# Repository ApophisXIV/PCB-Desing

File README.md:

# PCB-Desing
In this repo you'll find some PCBs I have designed across several years for differents projects

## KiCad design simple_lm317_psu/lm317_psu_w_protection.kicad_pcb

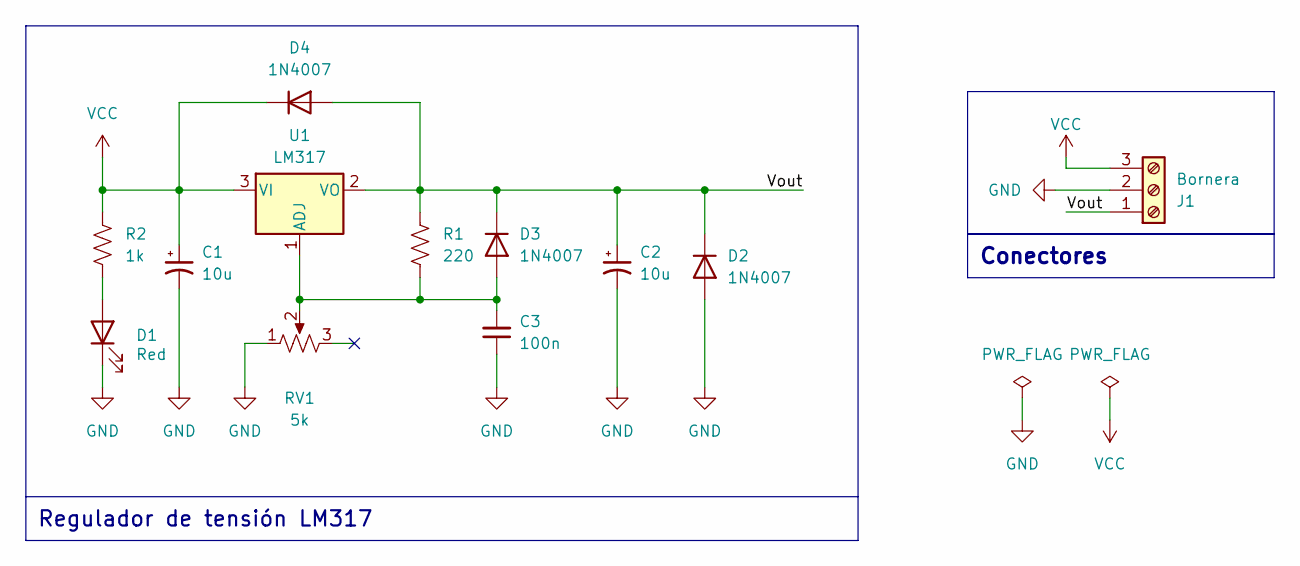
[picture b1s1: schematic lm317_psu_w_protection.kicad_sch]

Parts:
C1, C2: 10u; CP_Radial_D5.0mm_P2.00mm
C3: 100n; C_Disc_D5.0mm_W2.5mm_P2.50mm
D1: Red; LED_D5.0mm
D2, D3, D4: 1N4007; D_DO-41_SOD81_P10.16mm_Horizontal
J1: Bornera; TerminalBlock_bornier-3_P5.08mm
R1: 220; R_Axial_DIN0207_L6.3mm_D2.5mm_P7.62mm_Horizontal
R2: 1k; R_Axial_DIN0207_L6.3mm_D2.5mm_P7.62mm_Horizontal
RV1: 5k; Potentiometer_Alps_RK163_Single_Horizontal
U1: LM317; TO-220-3_Vertical

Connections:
/Vout: C2.1, D2.1 (K), D3.1 (K), D4.2 (A), J1.1, R1.1, U1.2 (VO)
GND: C1.2, C2.2, C3.1, D1.1 (K), D2.2 (A), J1.2, RV1.1
unnamed: D1.2 (A), R2.2
unnamed: C3.2, D3.2 (A), R1.2, RV1.2, U1.1 (ADJ)
VCC: C1.1, D4.1 (K), J1.3, R2.1, U1.3 (VI)

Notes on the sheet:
Conectores
Regulador de tensión LM317

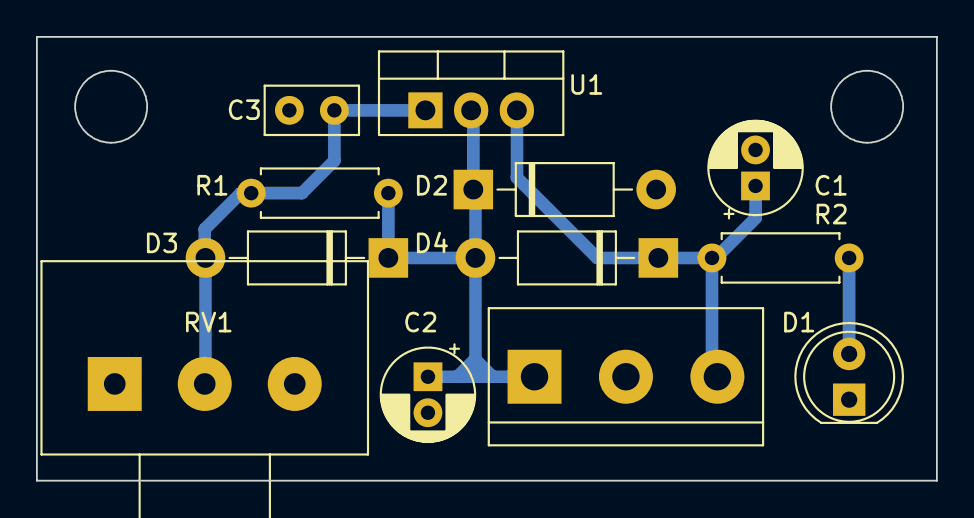
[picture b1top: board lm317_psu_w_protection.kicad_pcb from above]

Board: 2 copper layers, 50.0 x 24.7 mm, 12 parts (0 on the bottom side), 5 nets.

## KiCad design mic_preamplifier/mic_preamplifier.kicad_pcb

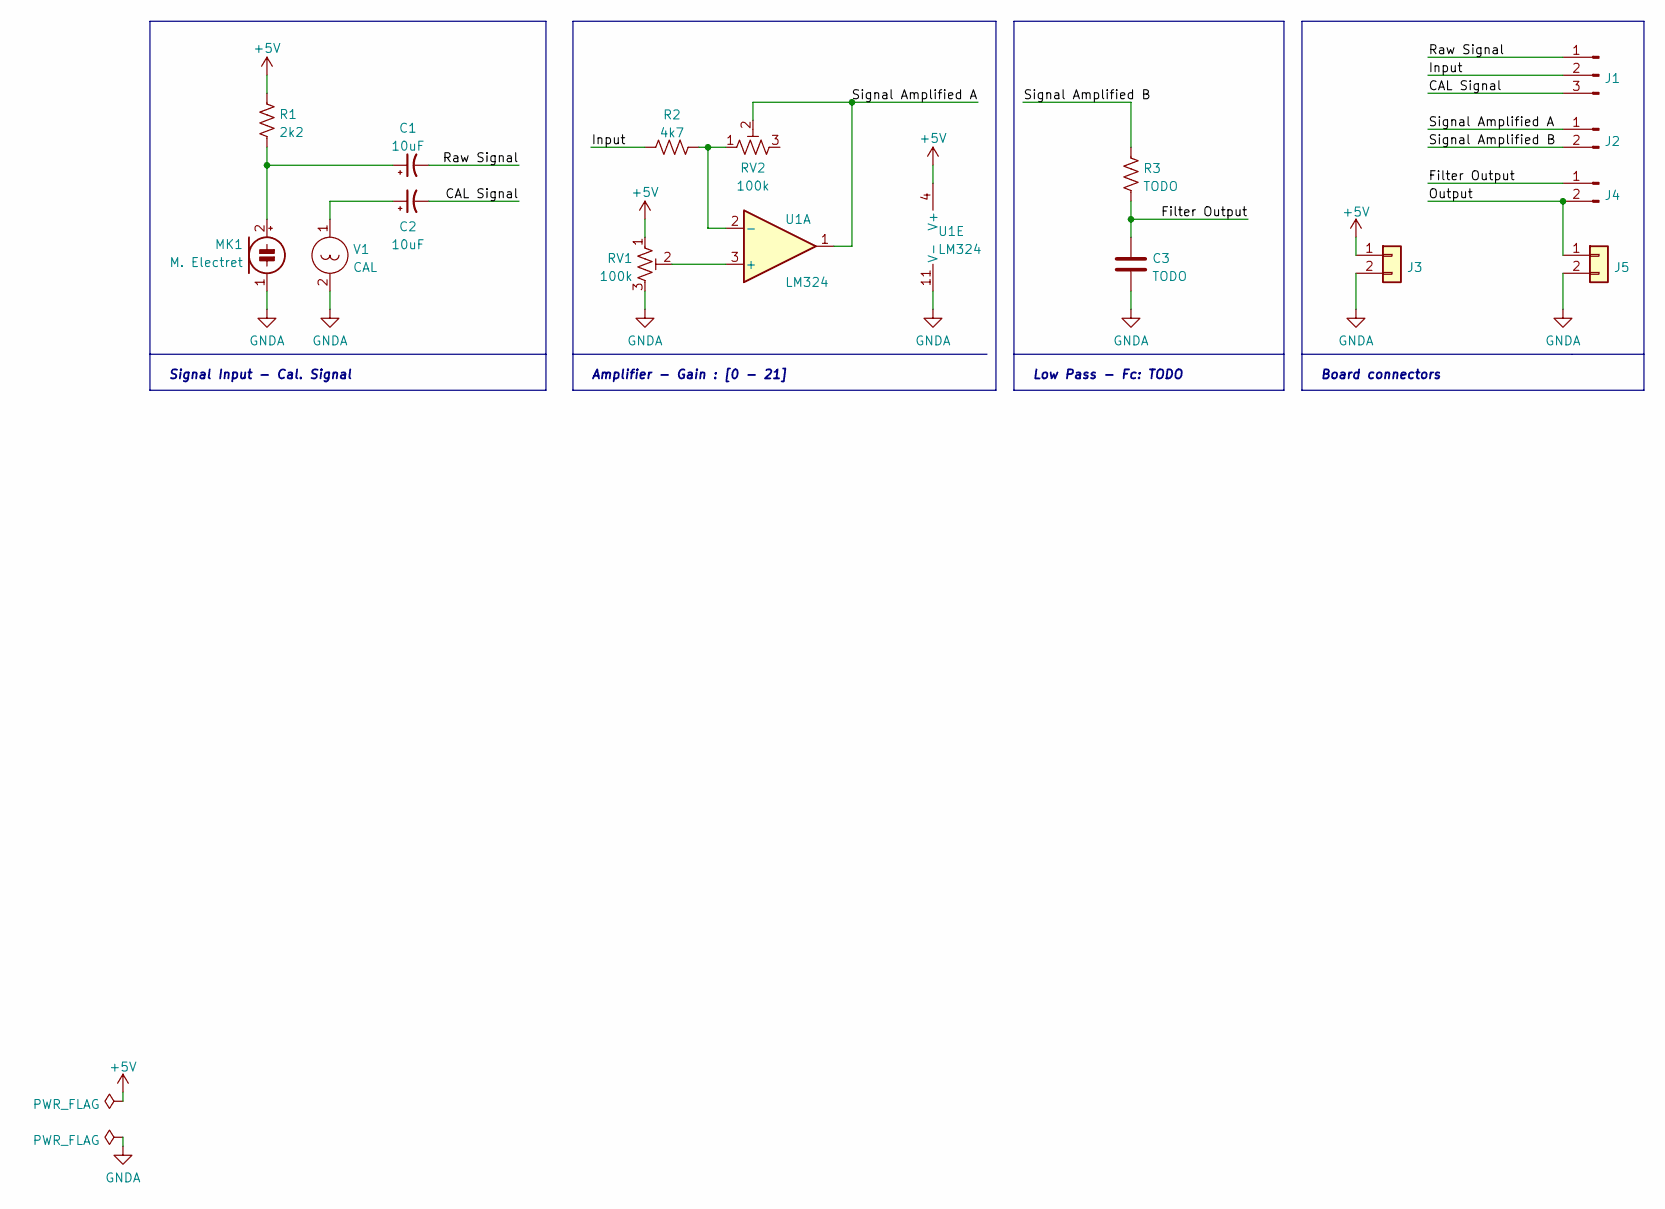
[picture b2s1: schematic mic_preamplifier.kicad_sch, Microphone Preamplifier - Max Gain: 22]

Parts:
C1, C2: 10uF; CP_Radial_D4.0mm_P2.00mm
C3: TODO; C_Disc_D3.8mm_W2.6mm_P2.50mm
J1: Conn_01x03_Male; PinHeader_1x03_P2.54mm_Vertical
J2, J4: Conn_01x02_Male; PinHeader_1x02_P2.54mm_Vertical
J3, J5: Conn_01x02; TerminalBlock_bornier-2_P5.08mm
MK1: M. Electret; PinHeader_1x02_P2.54mm_Vertical
R1: 2k2; R_Axial_DIN0207_L6.3mm_D2.5mm_P10.16mm_Horizontal
R2: 4k7; R_Axial_DIN0207_L6.3mm_D2.5mm_P10.16mm_Horizontal
R3: TODO; R_Axial_DIN0207_L6.3mm_D2.5mm_P10.16mm_Horizontal
RV1, RV2: 100k; Potentiometer_Bourns_3296W_Vertical
U1: LM324; DIP-14_W7.62mm_LongPads
V1: CAL; PinHeader_1x02_P2.54mm_Vertical

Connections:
+5V: J3.1, R1.1, RV1.1, U1.4 (V+)
/CAL Signal: C2.2, J1.3
/Filter Output: C3.1, J4.1, R3.1
/Input: J1.2, R2.1
/Output: J4.2, J5.1
/Raw Signal: C1.2, J1.1
/Signal Amplified A: J2.1, RV2.2, U1.1
/Signal Amplified B: J2.2, R3.2
GNDA: C3.2, J3.2, J5.2, MK1.1 (-), RV1.3, U1.11 (V-), V1.2
unnamed: C1.1, MK1.2 (+), R1.2
unnamed: C2.1, V1.1
unnamed: R2.2, RV2.1, U1.2 (-)
unnamed: RV1.2, U1.3 (+)

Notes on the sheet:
Signal Input - Cal. Signal
Amplifier - Gain : [0 - 21]
Low Pass - Fc: TODO
Board connectors

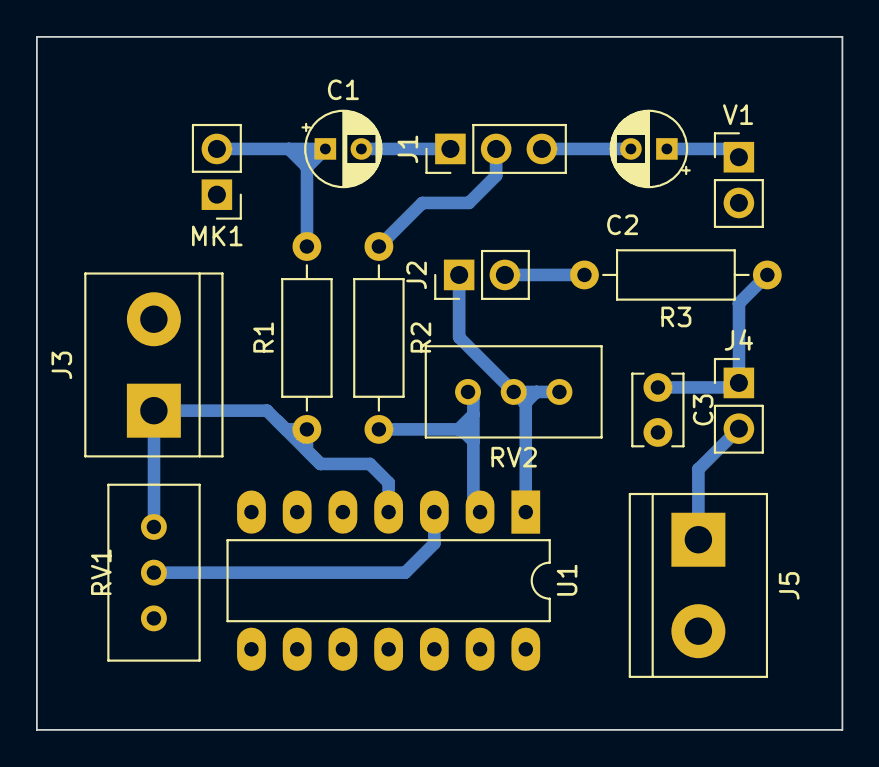
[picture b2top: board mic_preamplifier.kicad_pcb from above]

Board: 2 copper layers, 44.8 x 38.5 mm, 16 parts (0 on the bottom side), 13 nets.

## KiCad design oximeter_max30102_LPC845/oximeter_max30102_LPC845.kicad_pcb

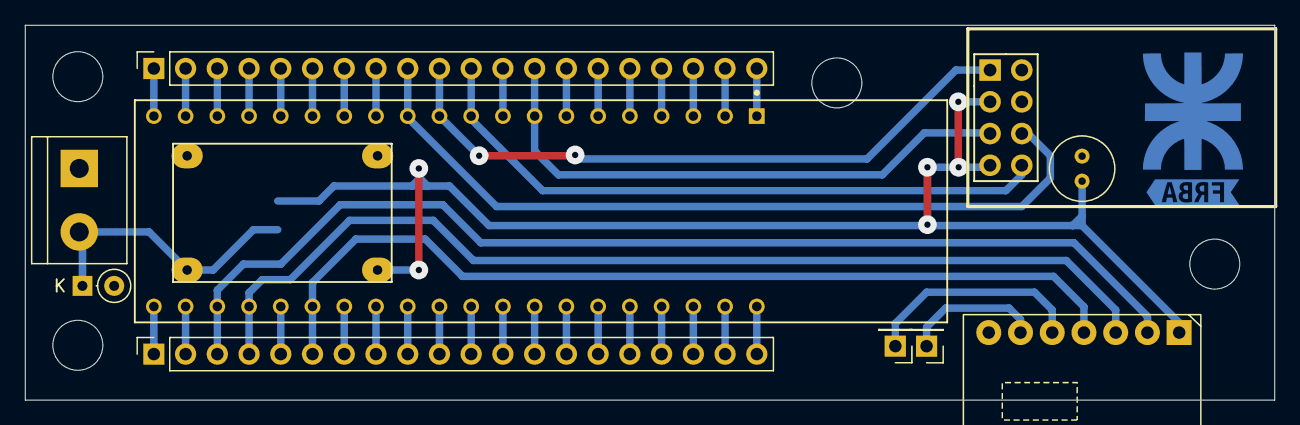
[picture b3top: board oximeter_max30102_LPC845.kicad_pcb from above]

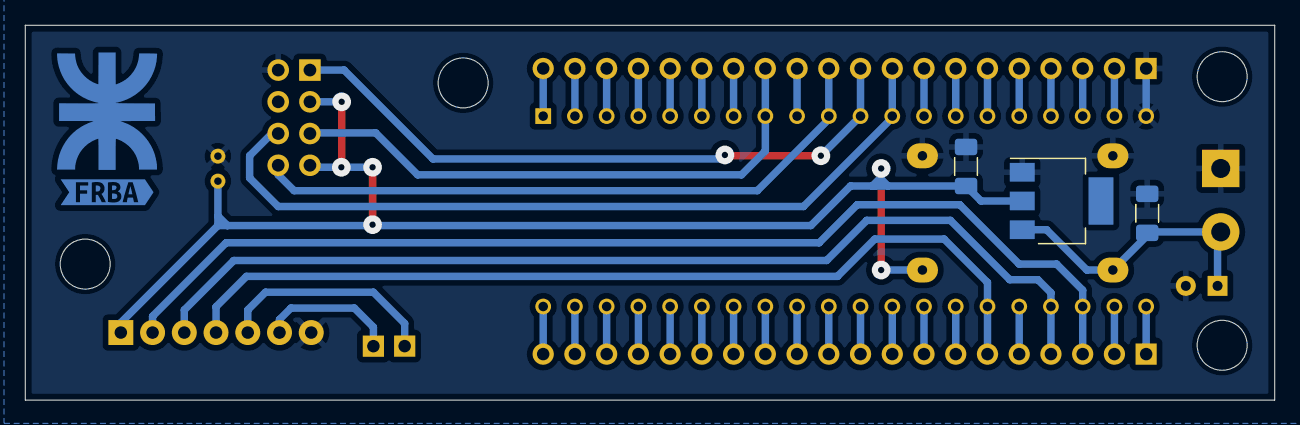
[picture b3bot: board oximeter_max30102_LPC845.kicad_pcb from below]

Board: 2 copper layers, 100.0 x 30.0 mm, 19 parts (4 on the bottom side), 44 nets.

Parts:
C1, C2: C; C_1206_3216Metric_Pad1.33x1.80mm_HandSolder
C3: C; C_Radial_D5.0mm_H7.0mm_P2.00mm
D1: D; D_DO-35_SOD27_P2.54mm_Vertical_KathodeUp
H1, H2, H3, H4: MountingHole; MountingHole_4mm
J1: VIN; TerminalBlock_bornier-2_P5.08mm
J7, J9: Conn_01x20_Socket; PinSocket_1x20_P2.54mm_Vertical
MD1: LPC845-BRK; NXP_Semiconductors-LPC845-BRK-MFG
TP1, TP2: TestPoint; PinHeader_1x01_P2.54mm_Vertical
U1: MAX30102-BRK
U2: ESP-01v090; ESP-01
U3: Mini360; Mini360_step-down
U4: AMS1117-3.3; SOT-223-3_TabPin2
kibuzzard-67073386: G***; kibuzzard-67073386

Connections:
+3V3: C2.1, C3.1, U1.1 (VIN), U2.3 (CH_PD), U2.7 (VCC), U3.4 (OUT+), U4.2 (VO)
/I2C_SCL: J9.3, MD1.23 (PIO0_10), U1.2 (SCL)
/I2C_SDA: J9.4, MD1.24 (PIO0_11), U1.3 (SDA)
/LED_B: J9.10, MD1.30 (PIO1_1/BLUE_LED)
/LED_G: J9.11, MD1.31 (PIO1_0/GREEN_LED)
/LED_R: J9.9, MD1.29 (PIO1_2/RED_LED)
/PIO0_0: J9.19, MD1.39 (PIO0_00)
/PIO0_1: J9.18, MD1.38 (PIO0_01)
/PIO0_2: J9.17, MD1.37 (PIO0_02/SWDIO)
/PIO0_3: J9.16, MD1.36 (PIO0_03/SWCLK)
/PIO0_4: J9.15, MD1.35 (PIO0_04/USER)
/PIO0_5: J7.12, MD1.9 (PIO0_05/~RESET)
/PIO0_5b: J9.14, MD1.34 (PIO0_05/~RESET)
/PIO0_6: J9.13, MD1.33 (PIO0_06)
/PIO0_7: J9.12, MD1.32 (PIO0_07/ADC/POT)
/PIO0_8: J7.2, MD1.19 (PIO0_08)
/PIO0_8b: J9.1, MD1.21 (PIO0_08)
/PIO0_9: J7.3, MD1.18 (PIO0_09)
/PIO0_9b: J9.2, MD1.22 (PIO0_09)
/PIO0_12: J9.5, MD1.25 (PIO0_12/ISP)
/PIO0_14: J9.7, MD1.27 (PIO0_14)
/PIO0_15: J9.8, MD1.28 (PIO0_15)
/PIO0_16: J7.20, MD1.1 (PIO0_16)
/PIO0_17: J7.19, MD1.2 (PIO0_17)
/PIO0_18: J7.18, MD1.3 (PIO0_18)
/PIO0_19: J7.17, MD1.4 (PIO0_19)
/PIO0_20: J7.16, MD1.5 (PIO0_20)
/PIO0_21: J7.15, MD1.6 (PIO0_21)
/PIO0_22: J7.14, MD1.7 (PIO0_22)
/PIO0_24: J7.11, MD1.10 (PIO0_24/TXD), U2.8 (URXD)
/PIO0_25: J7.10, MD1.11 (PIO0_25/RXD), U2.1 (UTXD)
/PIO0_27: J7.8, MD1.13 (PIO0_27)
/PIO0_28: J7.7, MD1.14 (PIO0_28)
/PIO0_29: J7.6, MD1.15 (PIO0_29)
/PIO0_30: J7.5, MD1.16 (PIO0_30)
/PIO0_31: J7.4, MD1.17 (PIO0_31)
/PRG_MODE: J7.9, MD1.12 (PIO0_26), U2.6 (GPIO0)
/RST: J7.13, MD1.8 (PIO0_23), U2.5 (RST)
/VDD: J9.20, MD1.40 (VDD)
/~INT: J9.6, MD1.26 (PIO0_13), U1.4 (INT)
GND: C1.2, C2.2, C3.2, D1.2 (A), J1.1, J7.1, MD1.20 (GND), U1.7 (GND), U2.2 (GND), U3.1 (IN-), U3.3 (OUT-), U4.1 (GND)
unnamed: C1.1, D1.1 (K), J1.2, U3.2 (IN+), U4.3 (VI)
unnamed: TP1.1, U1.5 (IRD)
unnamed: TP2.1, U1.6 (RD)

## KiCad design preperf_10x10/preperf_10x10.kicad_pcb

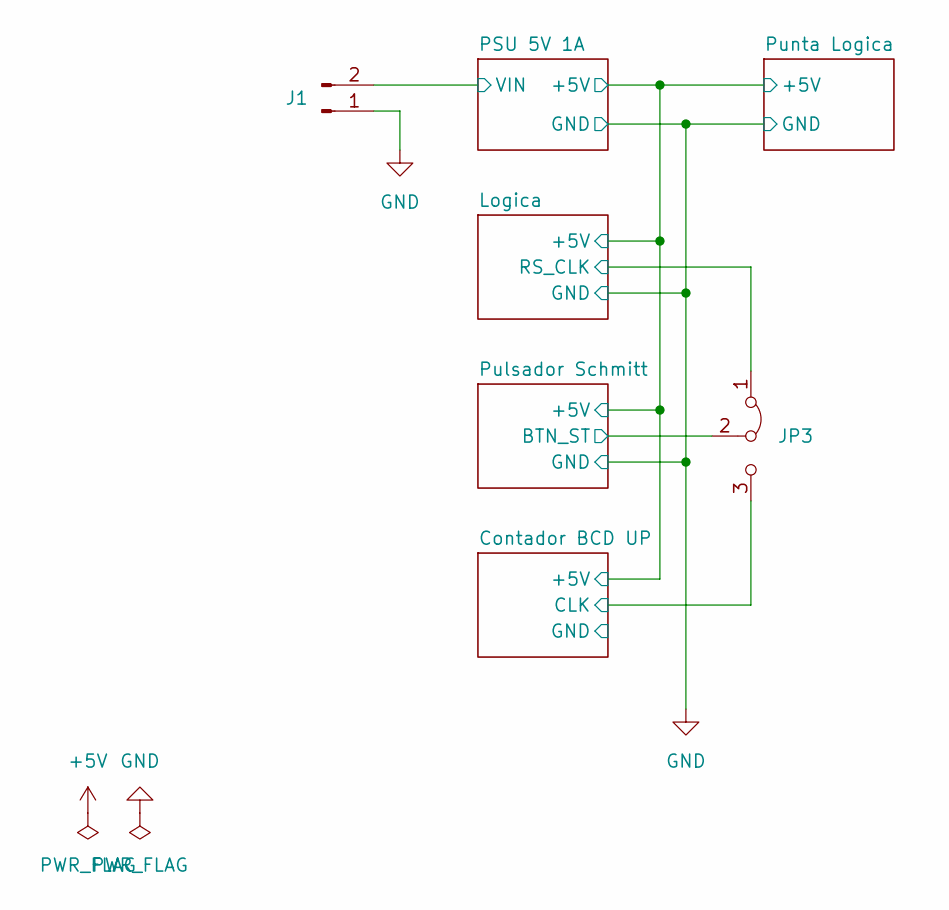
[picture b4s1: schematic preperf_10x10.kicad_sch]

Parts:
J1: Conn_01x02_Pin; Molex_KK-254_AE-6410-02A_1x02_P2.54mm_Vertical
JP3: Jumper_3_Bridged12; PinHeader_1x03_P2.54mm_Vertical

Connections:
/Contador BCD UP/CLK: JP3.3 (B); also elsewhere on the board
/Logica/RS_CLK: JP3.1 (A); also elsewhere on the board
/PSU 5V 1A/VIN: J1.2; also elsewhere on the board
/Pulsador Schmitt/BTN_ST: JP3.2 (C); also elsewhere on the board
GND: J1.1; also elsewhere on the board

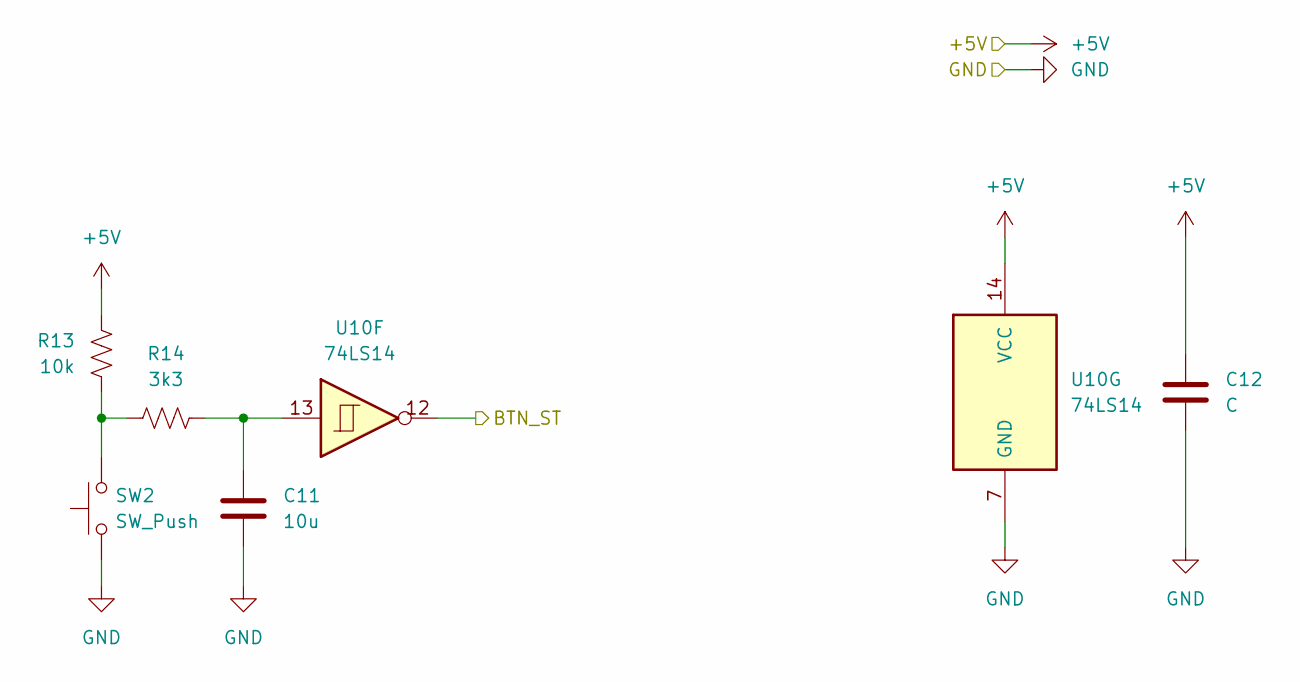
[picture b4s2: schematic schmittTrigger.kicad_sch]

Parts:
C11: 10u; C_Disc_D5.0mm_W2.5mm_P5.00mm
C12: C
R13: 10k; R_Axial_DIN0207_L6.3mm_D2.5mm_P7.62mm_Horizontal
R14: 3k3; R_Axial_DIN0207_L6.3mm_D2.5mm_P7.62mm_Horizontal
SW2: SW_Push; SW_PUSH_6mm_H7.3mm
U10: 74LS14; DIP-14_W7.62mm_Socket

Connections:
+5V: C12.1, R13.1, U10.14 (VCC); also elsewhere on the board
/Pulsador Schmitt/BTN_ST: U10.12; also elsewhere on the board
GND: C11.2, C12.2, SW2.1, U10.7 (GND); also elsewhere on the board
unnamed: C11.1, R14.2, U10.13
unnamed: R13.2, R14.1, SW2.2

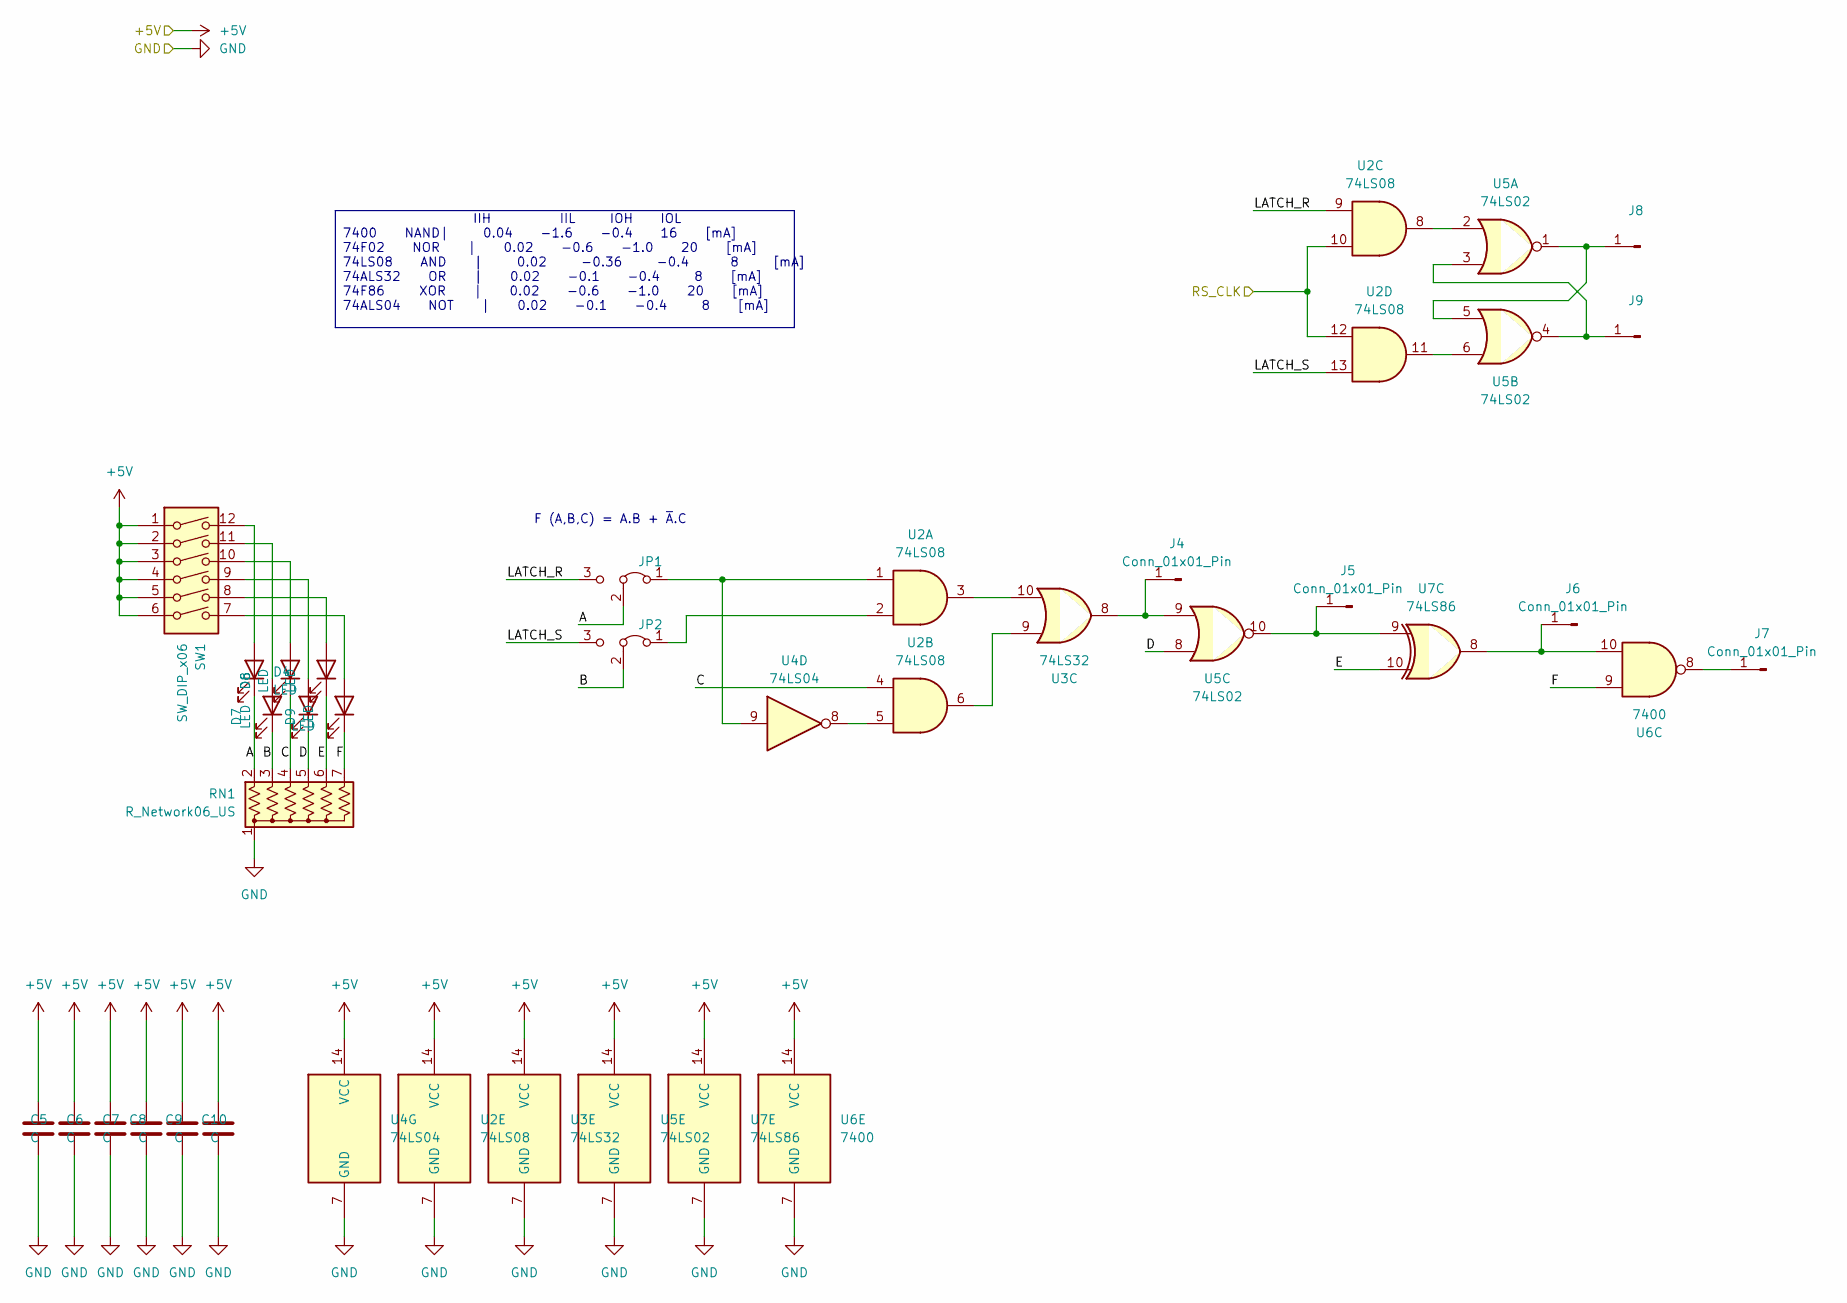
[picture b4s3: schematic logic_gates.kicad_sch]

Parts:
C5, C8, C9, C10: C; C_Disc_D5.0mm_W2.5mm_P2.50mm
C6, C7: C; C_Disc_D5.0mm_W2.5mm_P5.00mm
D4, D5, D6, D7, D8, D9: LED; LED_D3.0mm
J4, J5, J6, J7, J8, J9: Conn_01x01_Pin; PinHeader_1x01_P2.54mm_Vertical
JP1, JP2: Jumper_3_Bridged12; PinHeader_1x03_P2.54mm_Vertical
RN1: R_Network06_US; R_Array_SIP7
SW1: SW_DIP_x06; SW_DIP_SPSTx06_Slide_9.78x17.42mm_W7.62mm_P2.54mm
U2: 74LS08; DIP-14_W7.62mm_Socket
U3: 74LS32; DIP-14_W7.62mm_Socket
U4: 74LS04; DIP-14_W7.62mm_Socket
U5: 74LS02; DIP-14_W7.62mm_Socket
U6: 7400; DIP-14_W7.62mm_Socket
U7: 74LS86; DIP-14_W7.62mm_Socket

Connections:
+5V: C5.1, C6.1, C7.1, C8.1, C9.1, C10.1, SW1.1, SW1.2, SW1.3, SW1.4, SW1.5, SW1.6, U2.14 (VCC), U3.14 (VCC), U4.14 (VCC), U5.14 (VCC), U6.14 (VCC), U7.14 (VCC); also elsewhere on the board
/Logica/A: D4.1 (K), JP1.2 (C), RN1.2 (R1)
/Logica/B: D5.1 (K), JP2.2 (C), RN1.3 (R2)
/Logica/C: D6.1 (K), RN1.4 (R3), U2.4
/Logica/D: D7.1 (K), RN1.5 (R4), U5.8
/Logica/E: D8.1 (K), RN1.6 (R5), U7.10
/Logica/F: D9.1 (K), RN1.7 (R6), U6.9
/Logica/LATCH_R: JP1.3 (B), U2.9
/Logica/LATCH_S: JP2.3 (B), U2.13
/Logica/RS_CLK: U2.10, U2.12; also elsewhere on the board
GND: C5.2, C6.2, C7.2, C8.2, C9.2, C10.2, RN1.1 (common), U2.7 (GND), U3.7 (GND), U4.7 (GND), U5.7 (GND), U6.7 (GND), U7.7 (GND); also elsewhere on the board
unnamed: D4.2 (A), SW1.12
unnamed: D5.2 (A), SW1.11
unnamed: D6.2 (A), SW1.10
unnamed: D7.2 (A), SW1.9
unnamed: D8.2 (A), SW1.8
unnamed: D9.2 (A), SW1.7
unnamed: J4.1, U3.8, U5.9
unnamed: J5.1, U5.10, U7.9
unnamed: J6.1, U6.10, U7.8
unnamed: J7.1, U6.8
unnamed: J8.1, U5.1, U5.5
unnamed: J9.1, U5.3, U5.4
unnamed: JP1.1 (A), U2.1, U4.9
unnamed: JP2.1 (A), U2.2
unnamed: U2.3, U3.10
unnamed: U2.5, U4.8
unnamed: U2.6, U3.9
unnamed: U2.8, U5.2
unnamed: U2.11, U5.6

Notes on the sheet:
F (A,B,C) = A.B + ~{A}.C
IIH IIL IOH IOL 7400 NAND| 0.04 -1.6 -0.4 16 [mA] 74F02 NOR | 0.02 -0.6 -1.0 20 [mA] 74LS08 AND | 0.02 -0.36 -0.4 8 [mA] 74ALS32 OR | 0.02 -0.1 -0.4 8 [mA] 74F86 XOR | 0.02 -0.6 -1.0 20 [mA] 74ALS04 NOT | 0.02 -0.1 -0.4 8 [mA]

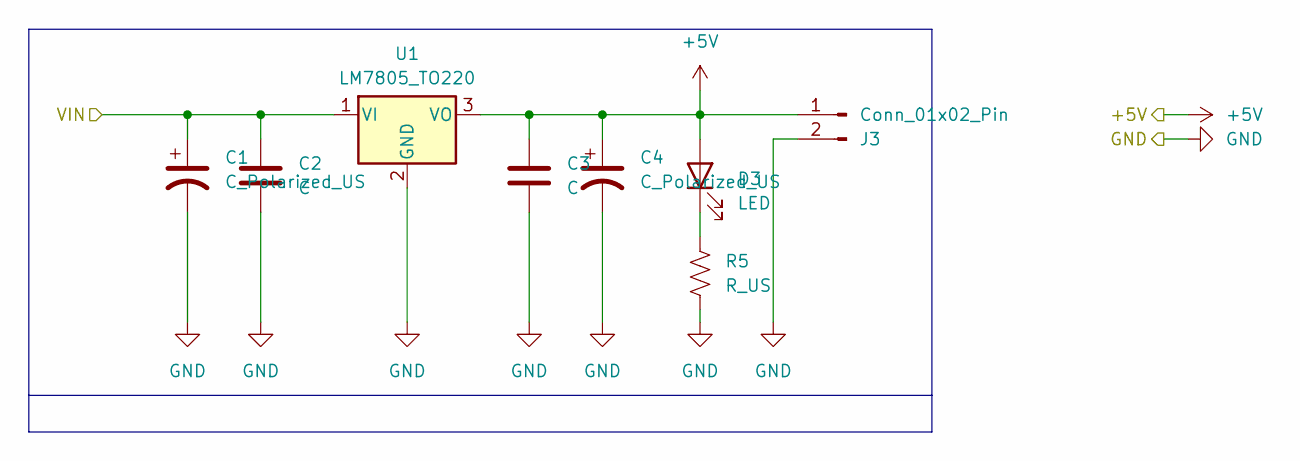
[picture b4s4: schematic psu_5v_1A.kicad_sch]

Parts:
C1, C4: C_Polarized_US; CP_Radial_D5.0mm_P2.50mm
C2, C3: C; C_Disc_D5.0mm_W2.5mm_P2.50mm
D3: LED; LED_D3.0mm
J3: Conn_01x02_Pin; Molex_KK-254_AE-6410-02A_1x02_P2.54mm_Vertical
R5: R_US; R_Axial_DIN0207_L6.3mm_D2.5mm_P7.62mm_Horizontal
U1: LM7805_TO220; TO-220-3_Vertical

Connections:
+5V: C3.1, C4.1, D3.2 (A), J3.1, U1.3 (VO); also elsewhere on the board
/PSU 5V 1A/VIN: C1.1, C2.1, U1.1 (VI); also elsewhere on the board
GND: C1.2, C2.2, C3.2, C4.2, J3.2, R5.2, U1.2 (GND); also elsewhere on the board
unnamed: D3.1 (K), R5.1

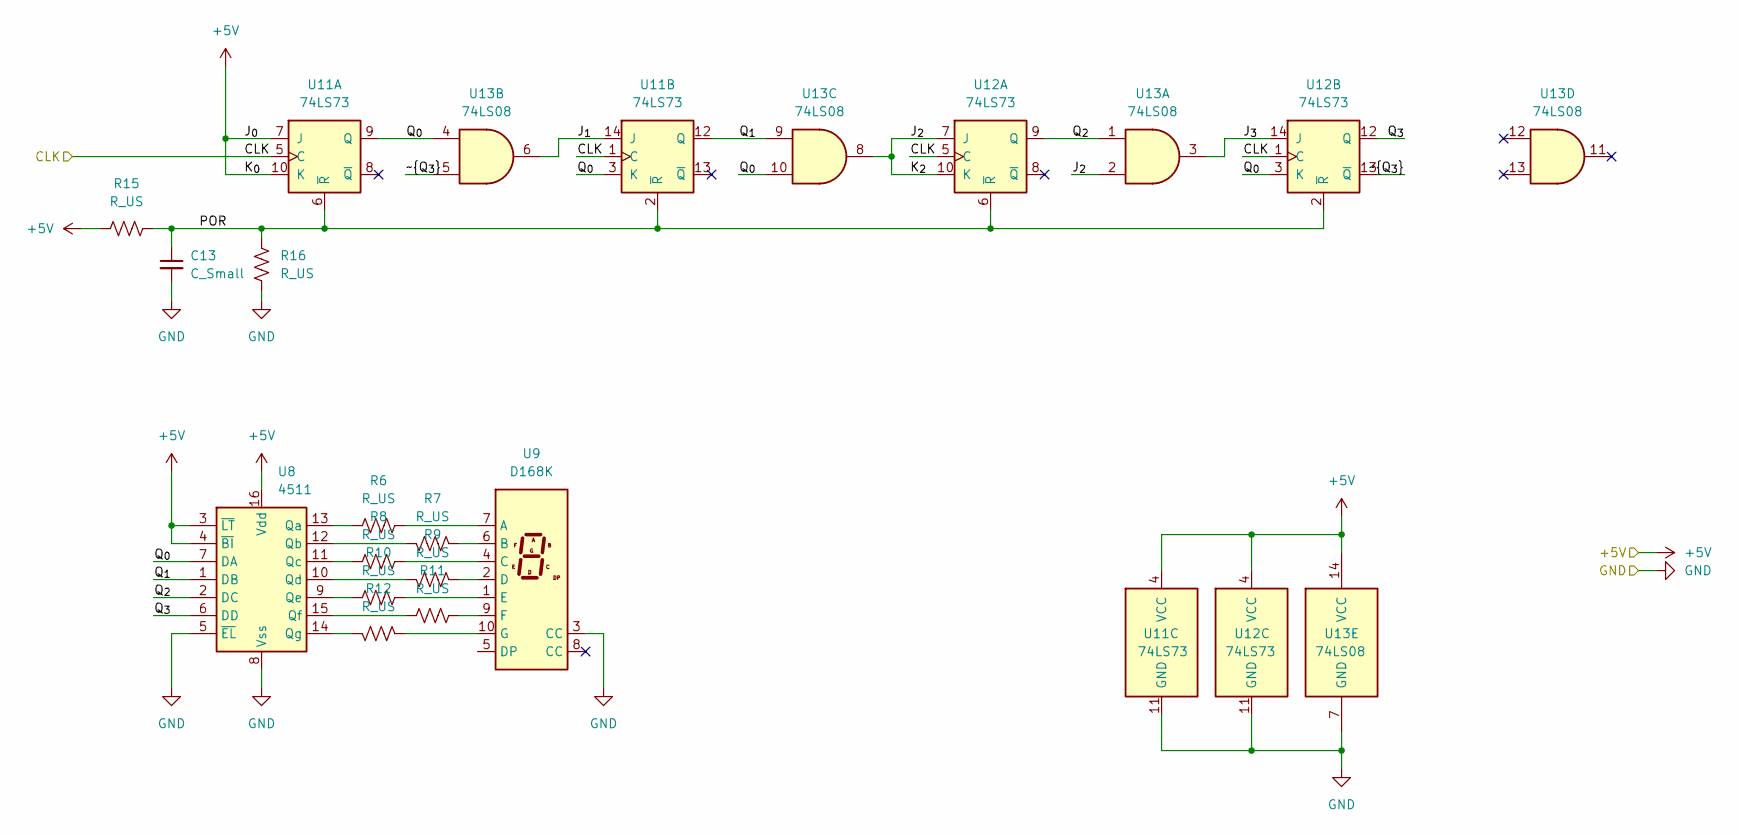
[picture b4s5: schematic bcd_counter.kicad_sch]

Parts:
C13: C_Small; CP_Radial_D5.0mm_P2.50mm
R6, R7, R8, R9, R10, R11, R12, R15, R16: R_US; R_Axial_DIN0207_L6.3mm_D2.5mm_P2.54mm_Vertical
U8: 4511; DIP-16_W7.62mm_Socket
U9: D168K; D1X8K
U11, U12: 74LS73; DIP-14_W7.62mm_Socket
U13: 74LS08; DIP-14_W7.62mm_Socket

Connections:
+5V: R15.1, U8.3 (~LT), U8.4 (~BI), U8.16 (Vdd), U11.4 (VCC), U11.7 (J), U11.10 (K), U12.4 (VCC), U13.14 (VCC); also elsewhere on the board
/Contador BCD UP/CLK: U11.1 (C), U11.5 (C), U12.1 (C), U12.5 (C); also elsewhere on the board
/Contador BCD UP/J_{1}: U11.14 (J), U13.6
/Contador BCD UP/J_{2}: U12.7 (J), U12.10 (K), U13.2, U13.8
/Contador BCD UP/J_{3}: U12.14 (J), U13.3
/Contador BCD UP/POR: C13.1, R15.2, R16.2, U11.2 (~R), U11.6 (~R), U12.2 (~R), U12.6 (~R)
/Contador BCD UP/Q_{0}: U8.7 (DA), U11.3 (K), U11.9 (Q), U12.3 (K), U13.4, U13.10
/Contador BCD UP/Q_{1}: U8.1 (DB), U11.12 (Q), U13.9
/Contador BCD UP/Q_{2}: U8.2 (DC), U12.9 (Q), U13.1
/Contador BCD UP/Q_{3}: U8.6 (DD), U12.12 (Q)
/Contador BCD UP/~Q_{3}: U12.13 (~Q), U13.5
GND: C13.2, R16.1, U8.5 (~EL), U8.8 (Vss), U9.3 (CC), U11.11 (GND), U12.11 (GND), U13.7 (GND); also elsewhere on the board
unnamed: R6.1, U8.13 (Qa)
unnamed: R7.2, U8.12 (Qb)
unnamed: R8.1, U8.11 (Qc)
unnamed: R9.2, U8.10 (Qd)
unnamed: R10.1, U8.9 (Qe)
unnamed: R11.1, U8.15 (Qf)
unnamed: R12.2, U8.14 (Qg)
unnamed: R6.2, U9.7 (A)
unnamed: R7.1, U9.6 (B)
unnamed: R8.2, U9.4 (C)
unnamed: R9.1, U9.2 (D)
unnamed: R10.2, U9.1 (E)
unnamed: R11.2, U9.9 (F)
unnamed: R12.1, U9.10 (G)

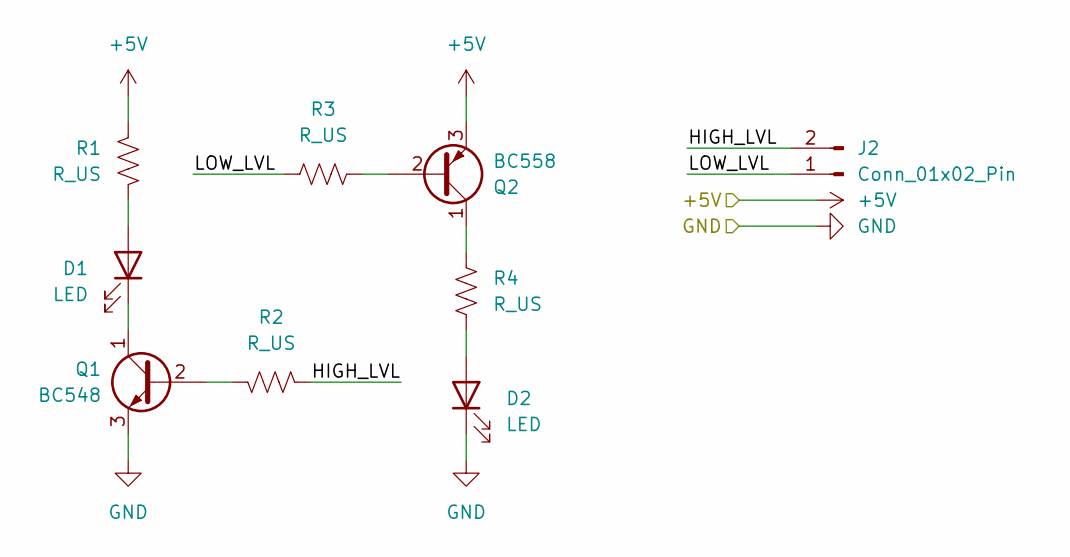
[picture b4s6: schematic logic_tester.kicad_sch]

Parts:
D1, D2: LED; LED_D3.0mm
J2: Conn_01x02_Pin; Molex_KK-254_AE-6410-02A_1x02_P2.54mm_Vertical
Q1: BC548; TO-92_Inline_Wide
Q2: BC558; TO-92_Inline_Wide
R1, R2, R3, R4: R_US; R_Axial_DIN0207_L6.3mm_D2.5mm_P2.54mm_Vertical

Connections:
+5V: Q2.3 (E), R1.1; also elsewhere on the board
/Punta Logica/HIGH_LVL: J2.2, R2.1
/Punta Logica/LOW_LVL: J2.1, R3.1
GND: D2.1 (K), Q1.3 (E); also elsewhere on the board
unnamed: D1.2 (A), R1.2
unnamed: D1.1 (K), Q1.1 (C)
unnamed: D2.2 (A), R4.1
unnamed: Q1.2 (B), R2.2
unnamed: Q2.2 (B), R3.2
unnamed: Q2.1 (C), R4.2
